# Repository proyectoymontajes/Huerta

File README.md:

# huerta
Automatizacion de huerta

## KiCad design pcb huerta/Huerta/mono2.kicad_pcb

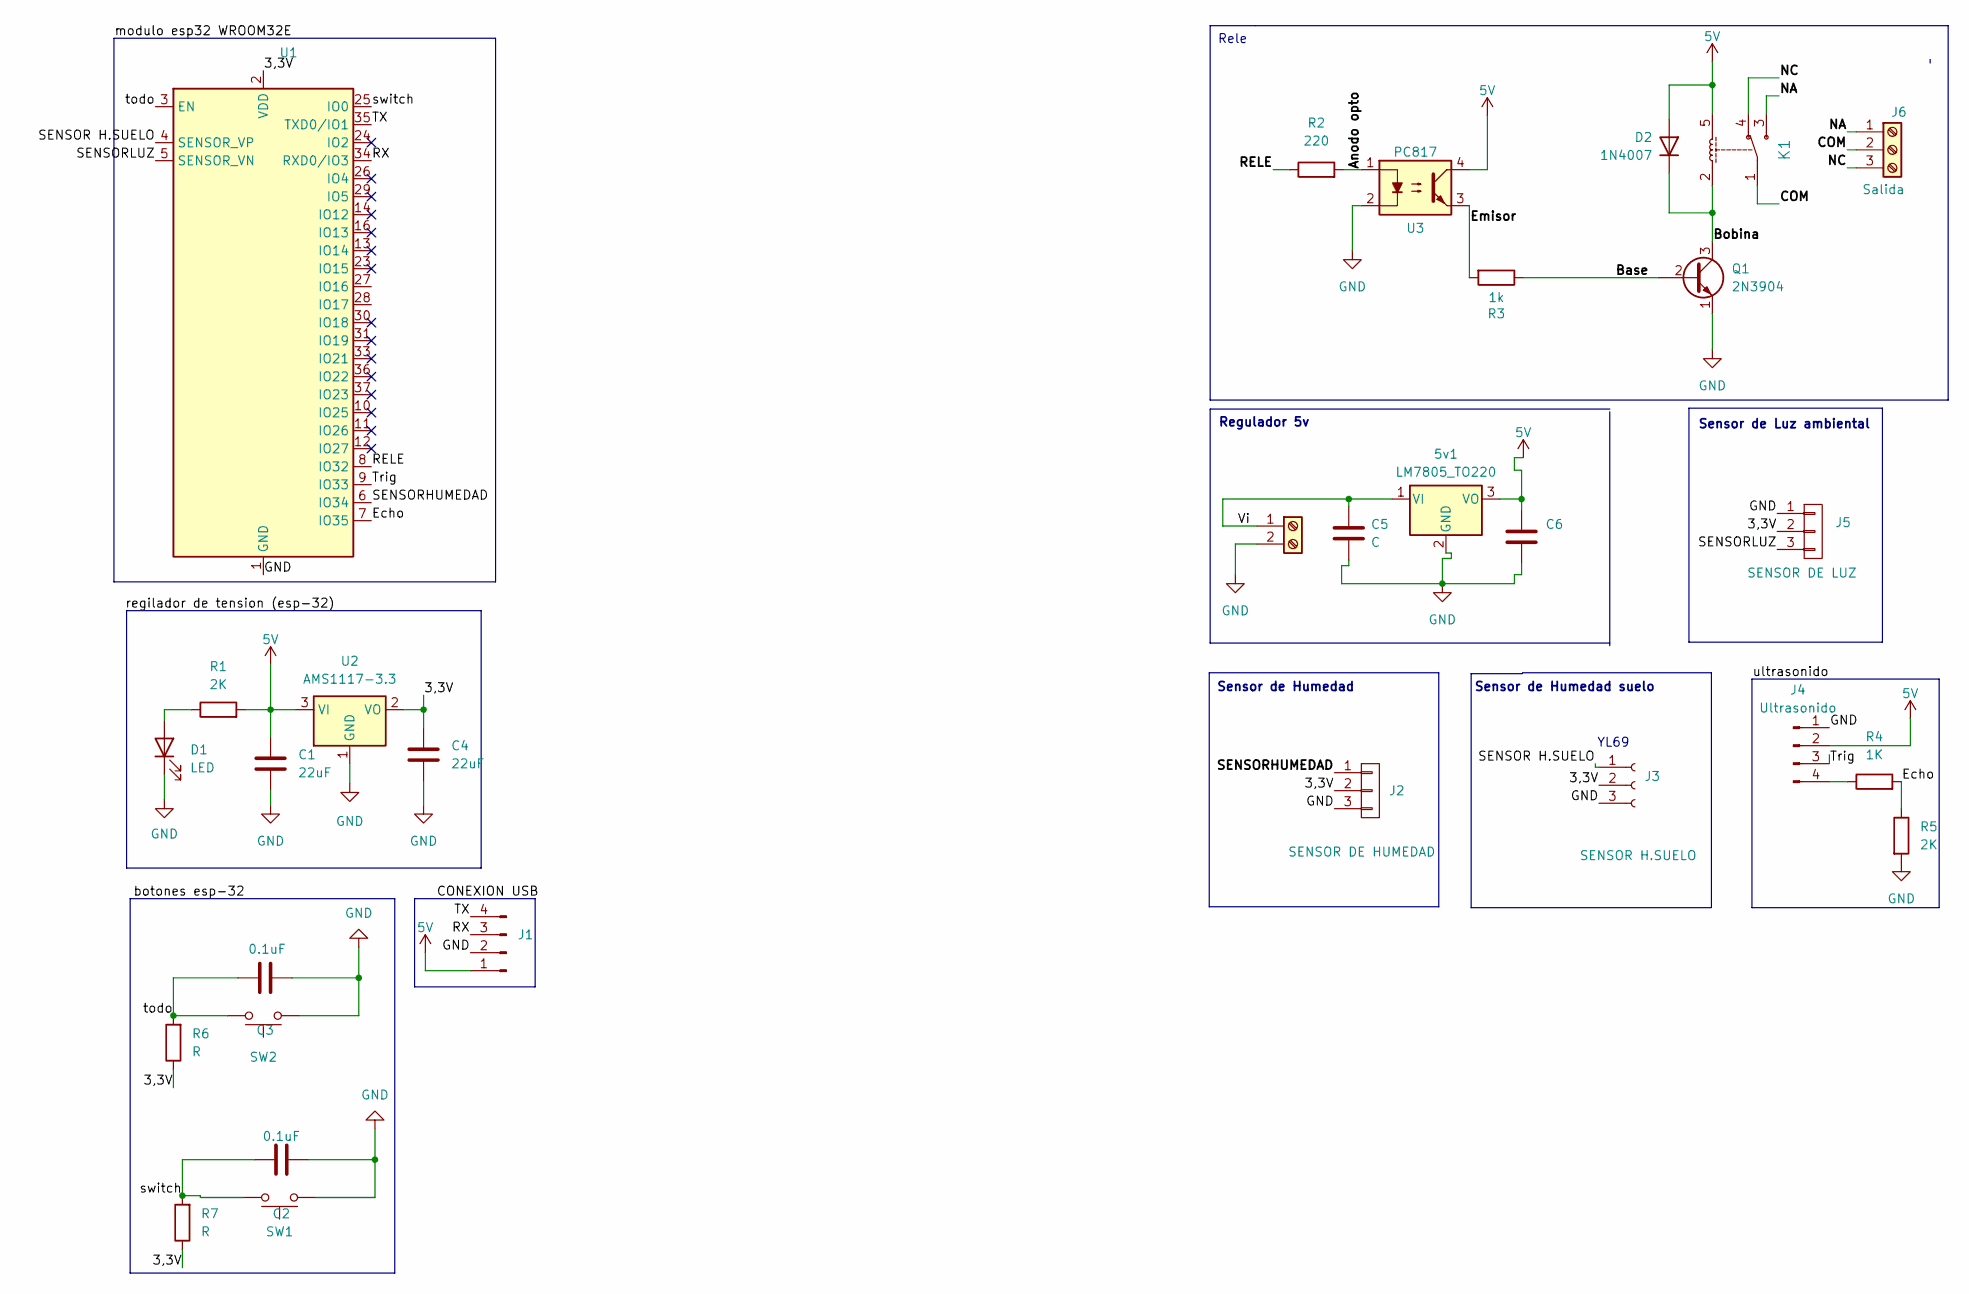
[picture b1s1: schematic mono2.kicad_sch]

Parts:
5v1: LM7805_TO220; TO-263-3_TabPin2
C1, C4: 22uF; CAP_ELEC_5x11mm
C2, C3: 0.1uF; C_1206_3216Metric_Pad1.33x1.80mm_HandSolder
C5, C6: C; CAP_ELEC_8x11.5mm
D1: LED; LED_1206_3216Metric_Pad1.42x1.75mm_HandSolder
D2: 1N4007; D_DO-41_SOD81_P10.16mm_Horizontal
J1: Conn_01x04_Pin; PinSocket_1x04_P2.54mm_Vertical
J2: SENSOR DE HUMEDAD; Pin_Strip_3
J3: SENSOR H.SUELO; Pin_Strip_3
J4: Ultrasonido; PinSocket_1x04_P2.54mm_Vertical
J5: SENSOR DE LUZ; Pin_Strip_3
J6: Salida; BORNERA3_AZUL
K1: RELAY_C; Relay_C
Q1: 2N3904; SOT-23_Handsoldering
R1, R5: 2K; R_1206_3216Metric_Pad1.30x1.75mm_HandSolder
R2: 220; R_1210_3225Metric_Pad1.30x2.65mm_HandSolder
R3: 1k; R_1210_3225Metric_Pad1.30x2.65mm_HandSolder
R4: 1K; R_1206_3216Metric_Pad1.30x1.75mm_HandSolder
R6, R7: R; R_1206_3216Metric_Pad1.30x1.75mm_HandSolder
SW1, SW2: SW_Push; SW_SPST_B3U-1000P-B
U1: ESP32-WROOM-32E; ESP32-WROOM-32D-HANDSOLDERING
U2: AMS1117-3.3; SOT-223-3_TabPin2
U3: PC817; DIP-4_W7.62mm
bornera1: bornera; BORNERA2_AZUL

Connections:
5V: 5v1.3 (VO), C1.1, C6.1, D2.2 (A), J1.1, J4.2, K1.5, R1.2, U2.3 (VI), U3.4
/3,3V: C4.1, J2.2, J3.2, J5.2, R6.1, R7.1, U1.2 (VDD), U2.2 (VO)
/Anodo opto: R2.2, U3.1
/Base: Q1.2 (B), R3.1
/Bobina: D2.1 (K), K1.2, Q1.3 (C)
/COM: J6.2, K1.1
/Echo: R4.2, R5.1, U1.7 (IO35)
/Emisor: R3.2, U3.3
/NA: J6.1, K1.3
/NC: J6.3, K1.4
/RELE: R2.1, U1.8 (IO32)
/RX: J1.3, U1.34 (RXD0/IO3)
/SENSOR H.SUELO: J3.1, U1.4 (SENSOR_VP)
/SENSORHUMEDAD: J2.1, U1.6 (IO34)
/SENSORLUZ: J5.3, U1.5 (SENSOR_VN)
/TX: J1.4, U1.35 (TXD0/IO1)
/Trig: J4.3, U1.9 (IO33)
/Vi: 5v1.1 (VI), C5.1, bornera1.1
/switch: C2.2, R7.2, SW1.2, U1.25 (IO0)
/todo: C3.2, R6.2, SW2.2, U1.3 (EN)
GND: 5v1.2 (GND), C1.2, C2.1, C3.1, C4.2, C5.2, C6.2, D1.1 (K), J1.2, J2.3, J3.3, J4.1, J5.1, Q1.1 (E), R5.2, SW1.1, SW2.1, U1.1 (GND), U1.15 (GND), U1.38 (GND), U1.39 (GND), U2.1 (GND), U3.2, bornera1.2
unnamed: D1.2 (A), R1.1
unnamed: J4.4, R4.1

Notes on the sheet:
YL69
Rele
Sensor de Humedad suelo
Sensor de Luz ambiental
Regulador 5v
Sensor de Humedad

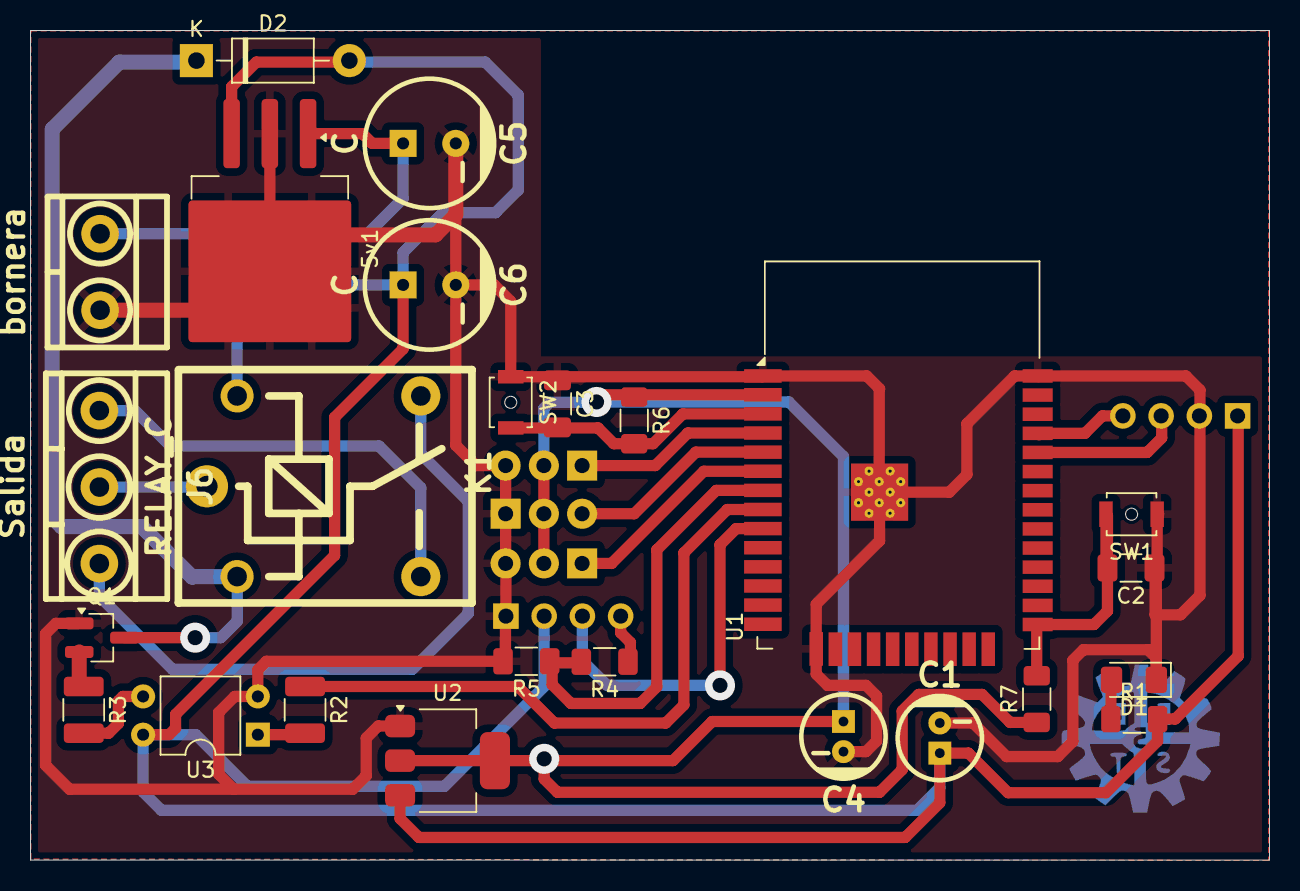
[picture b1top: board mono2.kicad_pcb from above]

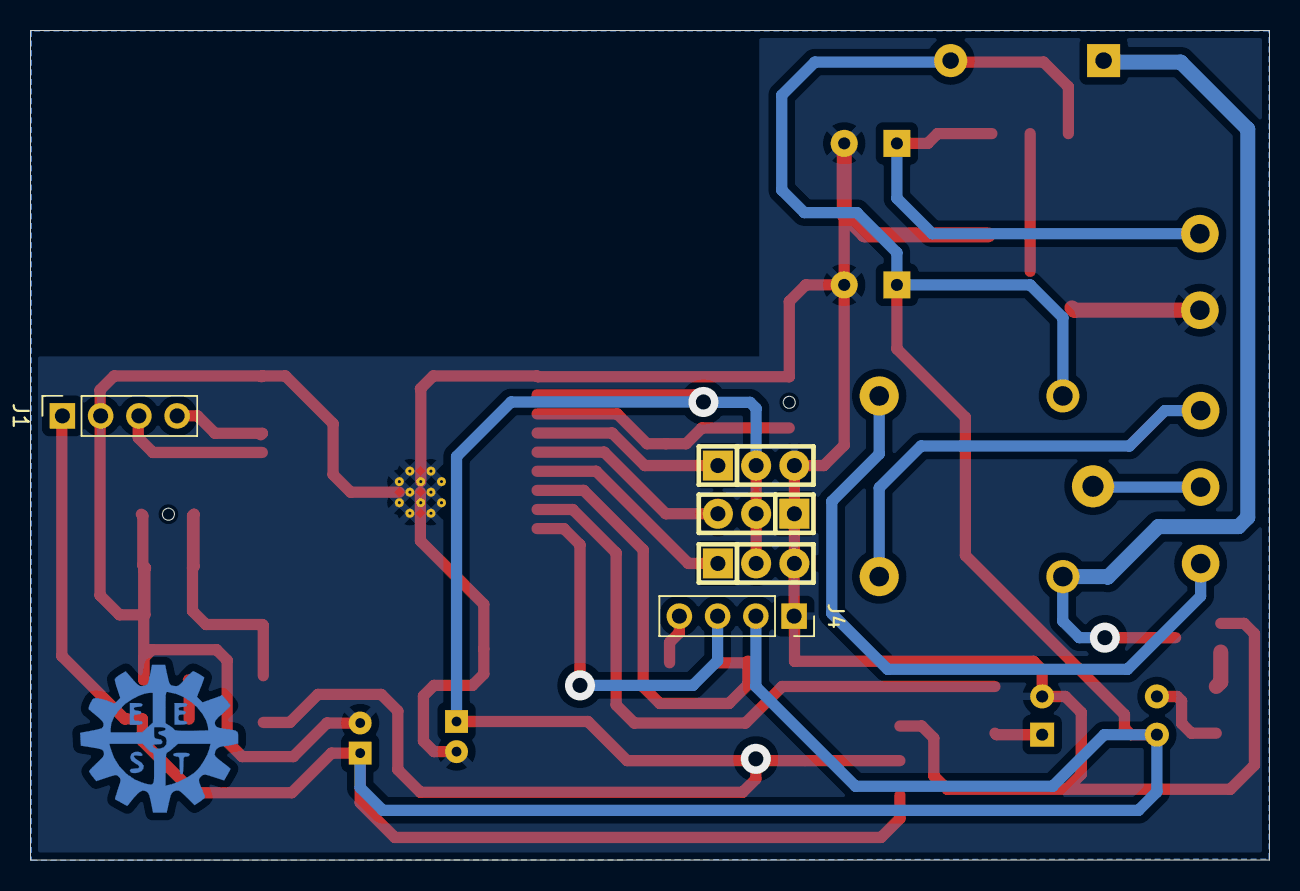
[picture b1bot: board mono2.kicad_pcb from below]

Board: 2 copper layers, 82.3 x 55.1 mm, 30 parts (5 on the bottom side), 23 nets.

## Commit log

2024-10-10 Placa de la huerta
    Placa de la huerta
